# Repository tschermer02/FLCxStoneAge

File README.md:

# FLCxStoneAge Electrical Documentation

This repository contains all electrical schematics, layouts, firmware, and documentation for the StoneAge waterjet positioning system.

## Sections
- `schematics/`: Electrical schematics (PDF and source)
- `pcb/`: PCB layouts and design files
- `firmware/`: Manual and Path Following code for microcontrollers
- `components/`: Component lists and data sheets
- `installation_guides/`: Guides for assembling and wiring
- `safety_docs/`: E-Stop systems, power cutoffs, compliance notes

---

### 📥 Usage
Clone or download this repository to access the full documentation.

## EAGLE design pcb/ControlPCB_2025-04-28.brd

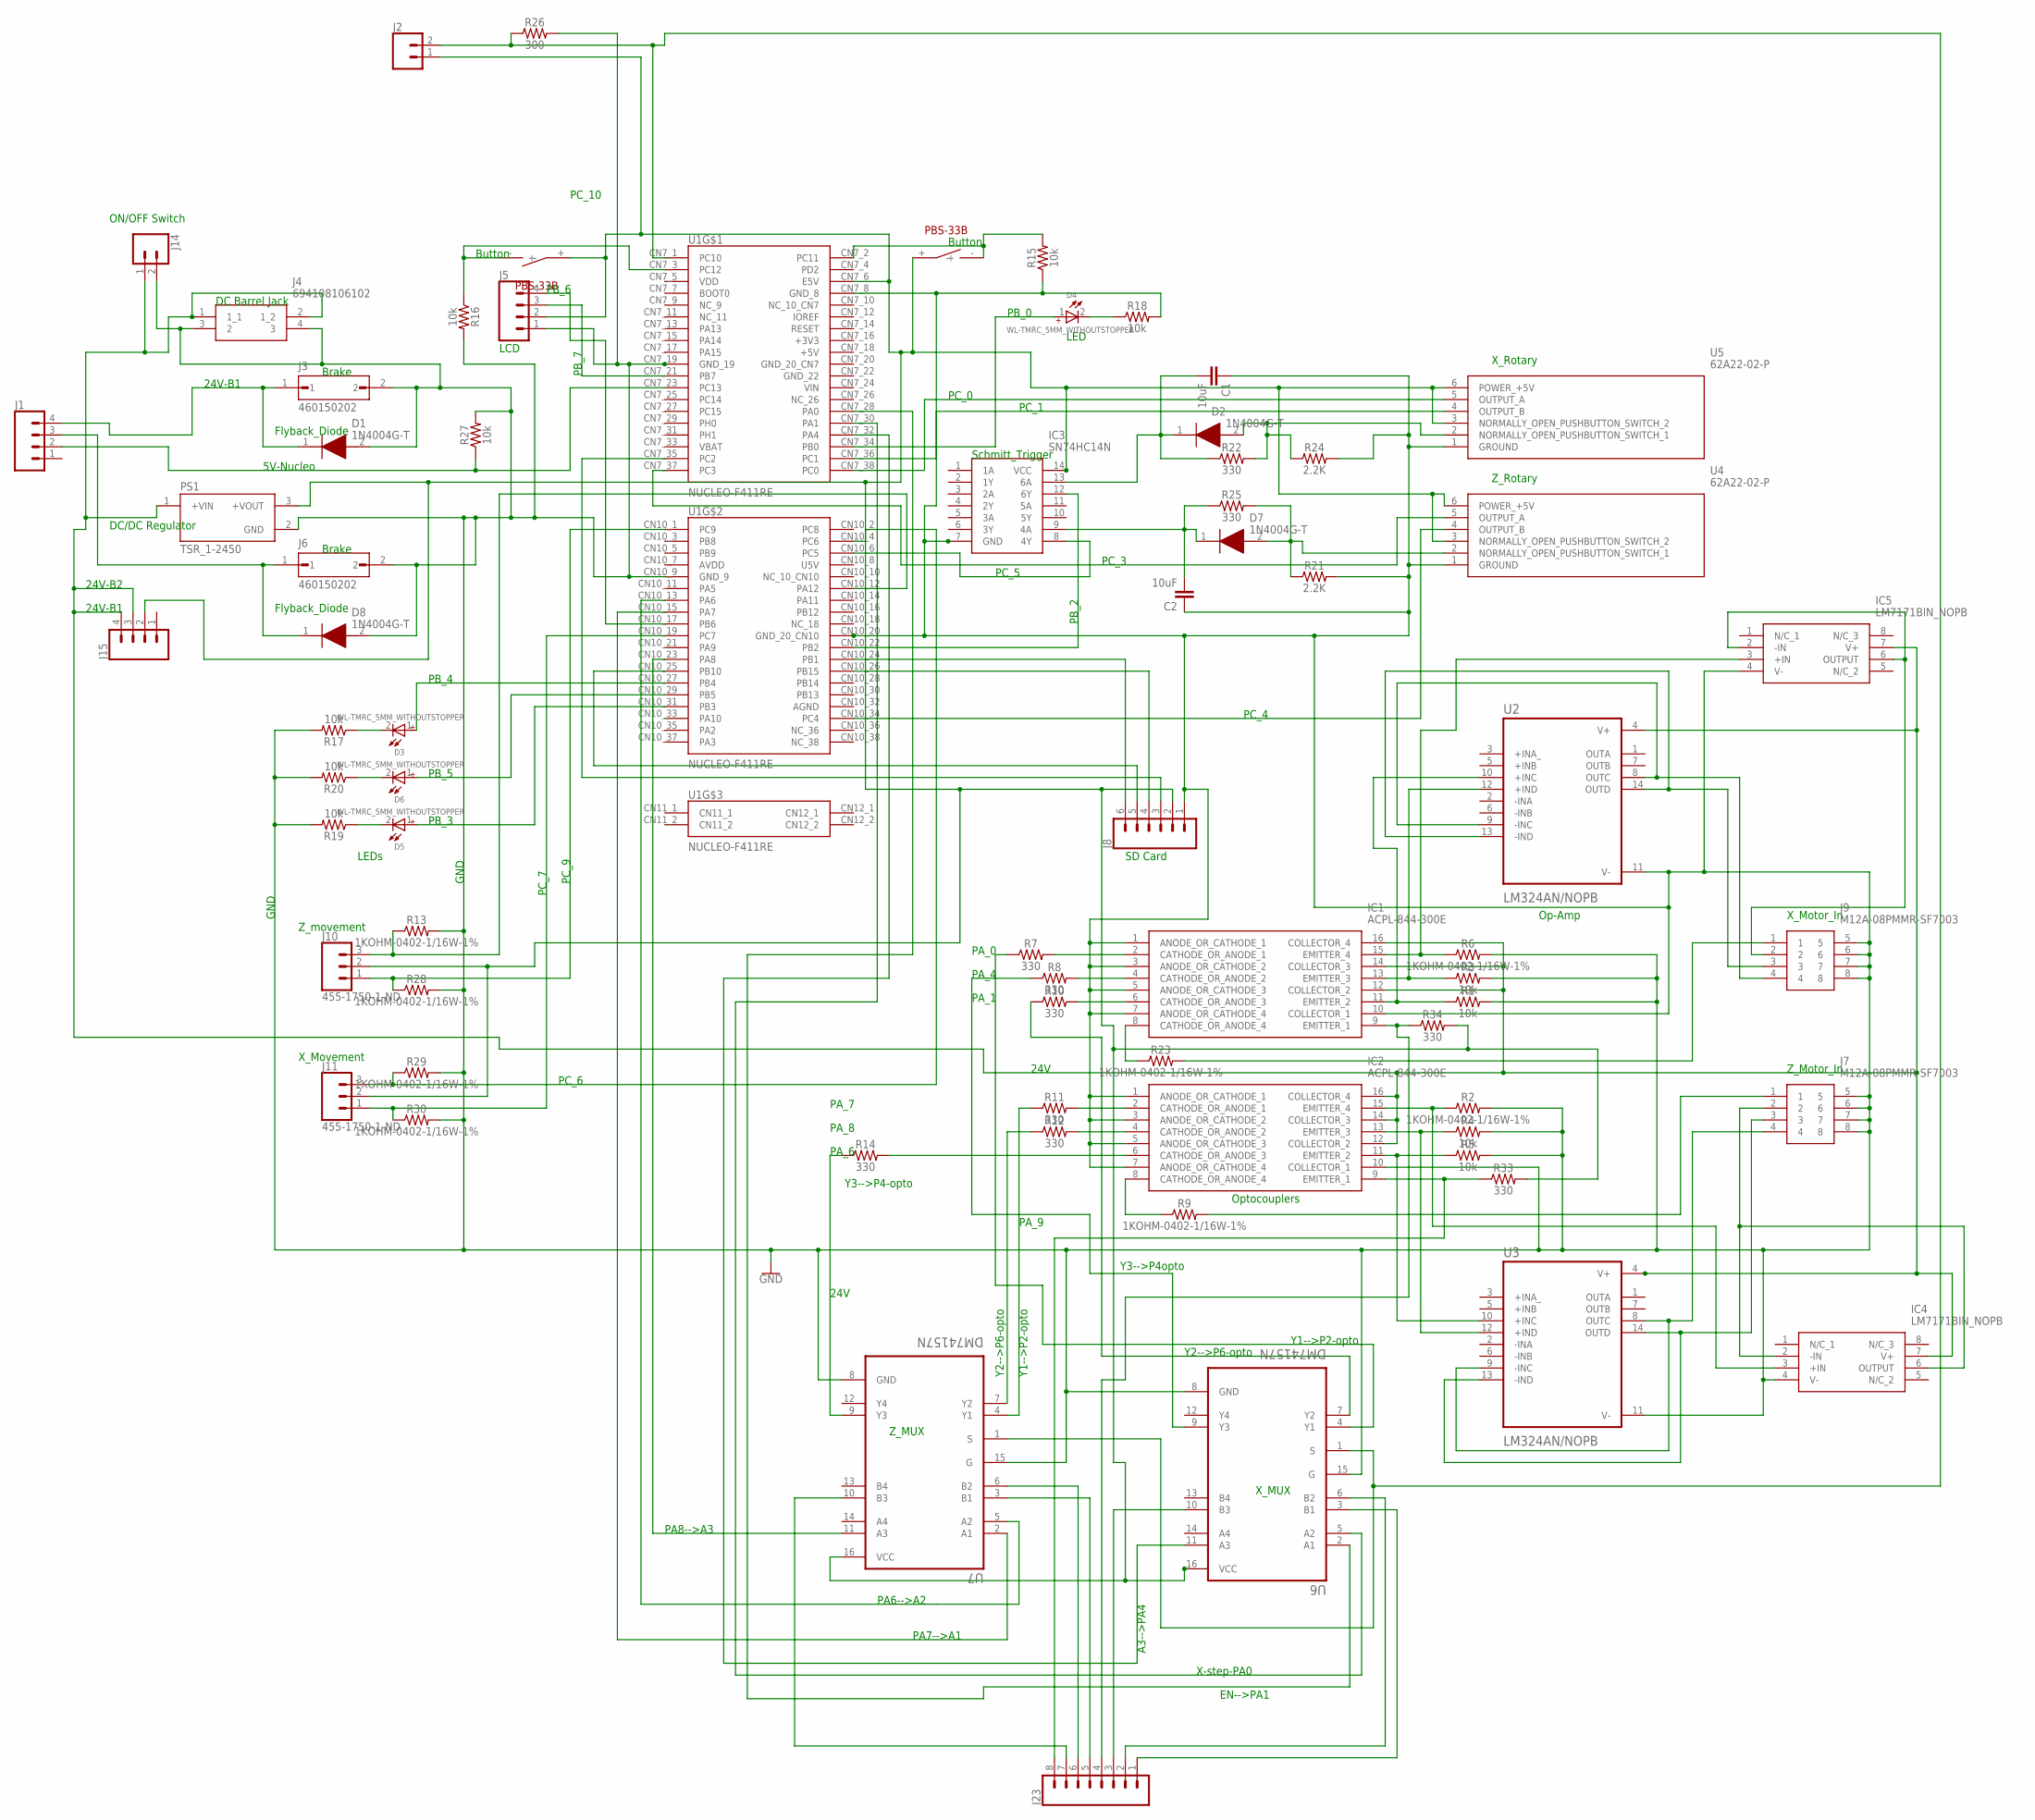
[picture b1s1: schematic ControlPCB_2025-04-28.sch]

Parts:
C1, C2: 10uF; 0603
D1, D2, D7, D8: 1N4004G-T; DIOAD1408W86L464D236
D3, D4, D5, D6: WL-TMRC_5MM_WITHOUTSTOPPER; WL-TMRC_5MM
IC1, IC2: ACPL-844-300E; DIP880W60P254L1984H450Q16N
IC3: SN74HC14N; DIP794W53P254L1930H508Q14N
IC4, IC5: LM7171BIN_NOPB; DIP794W53P254L959H508Q8N
J1, J15: CONN_04PTH; 1X04
J2, J14: CONN_02; 1X02
J3, J6: 460150202; MOLEX_460150202
J4: 694108106102
J5: CONN_04LOCK; 1X04_LOCK
J7, J9: M12A-08PMMR-SF7003; M12A08PMMRSF7003
J8: CONN_06SILK_FEMALE_PTH; 1X06
J10, J11: 455-1750-1-ND; 1X03
J23: CONN_08"; 1X08
PS1: TSR_1-2450; CONV_TSR_1-2450
R1, R3, R4, R5, R15, R16, R17, R18, R19, R20, R27: 10k; 0402
R2, R6, R9, R13, R23, R28, R29, R30: 1KOHM-0402-1/16W-1%; 0402
R7, R8, R10, R11, R12, R14, R22, R25, R33, R34: 330; 0402
R21, R24: 2.2K; 0402
R26: 300; 0603
U1: NUCLEO-F411RE; BOARD_NUCLEO-F411RE
U2, U3: LM324AN/NOPB; DIP794W45P254L1969H508Q14
U4, U5: 62A22-02-P; 62A2202P
U6, U7: DM74157N; DIP794W45P254L1918H533Q16
U$1, U$2: PBS-33B

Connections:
+3V3: U1.CN7_16 (+3V3)
+5V: U1.CN7_18 (+5V)
AGND: U1.CN10_32 (AGND)
AVDD: U1.CN10_7 (AVDD)
GND: C1.1, C2.1, D1.2 (A), D8.2 (A), IC1.1 (ANODE_OR_CATHODE_1), IC1.3 (ANODE_OR_CATHODE_2), IC1.5 (ANODE_OR_CATHODE_3), IC1.7 (ANODE_OR_CATHODE_4), IC1.10 (COLLECTOR_1), IC2.1 (ANODE_OR_CATHODE_1), IC2.3 (ANODE_OR_CATHODE_2), IC2.5 (ANODE_OR_CATHODE_3), IC2.7 (ANODE_OR_CATHODE_4), IC2.10 (COLLECTOR_1), IC3.7 (GND), IC4.4 (V-), IC5.4 (V-), J3.2, J4.3 (2), J4.4 (3), J5.1, J6.2, J7.5, J7.6, J7.7, J7.8, J8.1, J9.5, J9.6, J9.7, J9.8, J14.2, PS1.2 (GND), R1.2, R2.2, R3.2, R4.2, R5.2, R6.2, R13.2, R15.1, R16.2, R17.2, R18.2, R19.2, R20.2, R21.2, R24.2, R26.2, R27.2, R28.2, R29.2, R30.2, U1.CN7_8 (GND_8), U1.CN7_19 (GND_19), U1.CN10_9 (GND_9), U1.CN10_20 (GND_20_CN10), U2.11 (V-), U3.11 (V-), U4.1 (GROUND), U5.1 (GROUND), U6.8 (GND), U6.15 (G), U7.8 (GND), U7.15 (G)
GND_20_CN7: U1.CN7_20 (GND_20_CN7)
GND_22: U1.CN7_22 (GND_22)
unnamed: J10.1, R28.1, U1.CN10_1 (PC9)
unnamed: J9.4, U2.8 (OUTC), U2.9 (-INC)
unnamed: C2.2, D7.1 (K), IC3.9 (4A), R25.1
unnamed: IC2.9 (EMITTER_1), J23.8, R33.1
unnamed: IC2.2 (CATHODE_OR_ANODE_1), R11.2
unnamed: D8.1 (K), J1.3, J6.1
unnamed: J7.3, U3.13 (-IND), U3.14 (OUTD)
unnamed: IC2.8 (CATHODE_OR_ANODE_4), R9.1
unnamed: IC3.14 (VCC), J2.1, J5.2, J8.2, J10.2, J11.2, J15.2, PS1.3 (+VOUT), R33.2, R34.2, U1.CN7_6 (E5V), U4.3 (NORMALLY_OPEN_PUSHBUTTON_SWITCH_2), U4.6 (POWER_+5V), U5.3 (NORMALLY_OPEN_PUSHBUTTON_SWITCH_2), U5.6 (POWER_+5V), U6.16 (VCC), U7.16 (VCC), U$1.+, U$2.+
unnamed: J7.4, U3.8 (OUTC), U3.9 (-INC)
unnamed: D1.1 (K), J1.4, J3.1
unnamed: J7.1, R9.2
unnamed: IC1.4 (CATHODE_OR_ANODE_2), R8.2
unnamed: IC4.2 (-IN), IC4.6 (OUTPUT), J7.2
unnamed: R10.1, U6.7 (Y2)
unnamed: IC1.15 (EMITTER_4), IC5.3 (+IN), R6.1
unnamed: J23.7, U7.10 (B3)
unnamed: J23.6, U7.6 (B2)
unnamed: IC1.8 (CATHODE_OR_ANODE_4), R23.1
unnamed: IC5.2 (-IN), IC5.6 (OUTPUT), J9.2
unnamed: J23.5, U7.3 (B1)
unnamed: J1.2, R27.1, U1.CN7_23 (PC13)
unnamed: R16.1, U1.CN7_3 (PC12), U$2.-
unnamed: R15.2, U1.CN7_2 (PC11), U$1.-
unnamed: IC3.12 (6Y), U1.CN10_22 (PB2)
unnamed: U1.CN7_32 (PA4), U6.11 (A3)
unnamed: IC2.11 (EMITTER_2), R5.1, U3.10 (+INC)
unnamed: U1.CN7_37 (PC3), U4.5 (OUTPUT_A)
unnamed: R12.1, U7.7 (Y2)
unnamed: IC1.2 (CATHODE_OR_ANODE_1), R7.2
unnamed: IC1.12 (COLLECTOR_2), IC1.14 (COLLECTOR_3), IC1.16 (COLLECTOR_4), IC2.12 (COLLECTOR_2), IC2.14 (COLLECTOR_3), IC2.16 (COLLECTOR_4), IC4.7 (V+), IC5.7 (V+), J4.1 (1_1), J4.2 (1_2), J14.1, J15.3, J15.4, PS1.1 (+VIN), U2.4 (V+), U3.4 (V+)
unnamed: R7.1, U6.4 (Y1)
unnamed: IC1.6 (CATHODE_OR_ANODE_3), R10.2
unnamed: IC2.4 (CATHODE_OR_ANODE_2), R12.2
unnamed: U1.CN10_15 (PA7), U7.2 (A1)
unnamed: D7.2 (A), R21.1, R25.2, U4.2 (NORMALLY_OPEN_PUSHBUTTON_SWITCH_1)
unnamed: R11.1, U7.4 (Y1)
unnamed: U1.CN7_38 (PC0), U5.5 (OUTPUT_A)
unnamed: IC1.9 (EMITTER_1), J23.4, R34.1
unnamed: J9.3, U2.13 (-IND), U2.14 (OUTD)
unnamed: U1.CN10_34 (PC4), U4.4 (OUTPUT_B)
unnamed: C1.2, D2.1 (K), IC3.13 (6A), R22.1
unnamed: D4.1 (+), U1.CN7_34 (PB0)
unnamed: J5.4, U1.CN10_17 (PB6)
unnamed: D6.2 (-), R20.1
unnamed: D5.2 (-), R19.1
unnamed: D4.2 (-), R18.1
unnamed: D3.2 (-), R17.1
unnamed: J8.4, U1.CN10_26 (PB15)
unnamed: J8.5, U1.CN10_25 (PB10)
unnamed: R14.1, U7.9 (Y3)
unnamed: J9.1, R23.2
unnamed: U1.CN10_13 (PA6), U7.5 (A2)
unnamed: U1.CN7_30 (PA1), U6.5 (A2)
unnamed: U1.CN7_28 (PA0), U6.2 (A1)
unnamed: D3.1 (+), U1.CN10_27 (PB4)
unnamed: D6.1 (+), U1.CN10_29 (PB5)
unnamed: J5.3, U1.CN7_21 (PB7)
unnamed: J23.3, U6.10 (B3)
unnamed: J23.2, U6.6 (B2)
unnamed: D5.1 (+), U1.CN10_31 (PB3)
unnamed: U1.CN10_23 (PA8), U7.11 (A3)
unnamed: U1.CN7_36 (PC1), U5.4 (OUTPUT_B)
unnamed: J23.1, U6.3 (B1)
unnamed: D2.2 (A), R22.2, R24.1, U5.2 (NORMALLY_OPEN_PUSHBUTTON_SWITCH_1)
unnamed: J8.6, U1.CN10_24 (PB1)
unnamed: IC3.8 (4Y), U1.CN10_6 (PC5)
unnamed: J8.3, U1.CN7_35 (PC2)
unnamed: J2.2, R26.1, U1.CN7_1 (PC10), U6.1 (S), U7.1 (S)
unnamed: J10.3, R13.1, U1.CN10_12 (PA12)
unnamed: J11.3, R29.1, U1.CN10_4 (PC6)
unnamed: J11.1, R30.1, U1.CN10_19 (PC7)
unnamed: IC1.13 (EMITTER_3), R3.1, U2.12 (+IND)
unnamed: IC2.13 (EMITTER_3), R4.1, U3.12 (+IND)
unnamed: IC2.6 (CATHODE_OR_ANODE_3), R14.2
unnamed: R8.1, U6.9 (Y3)
unnamed: IC1.11 (EMITTER_2), R1.1, U2.10 (+INC)
unnamed: IC2.15 (EMITTER_4), IC4.3 (+IN), R2.1
U5V: U1.CN10_8 (U5V)
VBAT: U1.CN7_33 (VBAT)
VDD: U1.CN7_5 (VDD)

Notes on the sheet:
X-step-PA0
EN-->PA1
Y2-->P6-opto
A3-->PA4
Y3-->P4opto
Y1-->P2-opto
Y3-->P4-opto
ON/OFF Switch
DC Barrel Jack
Brake
Flyback_Diode
DC/DC Regulator
LEDs
X_Movement
Z_movement
SD Card
Optocouplers
Op-Amp
X_Motor_In
Z_Motor_In
Schmitt_Trigger
X_Rotary
Z_Rotary
X_MUX
Z_MUX
LED
Button
LCD
PC_9
GND
PC_6
PC_7
24V
PC_0
PC_1
PB_0
PA_0
PA_1
PA_4
PA_8

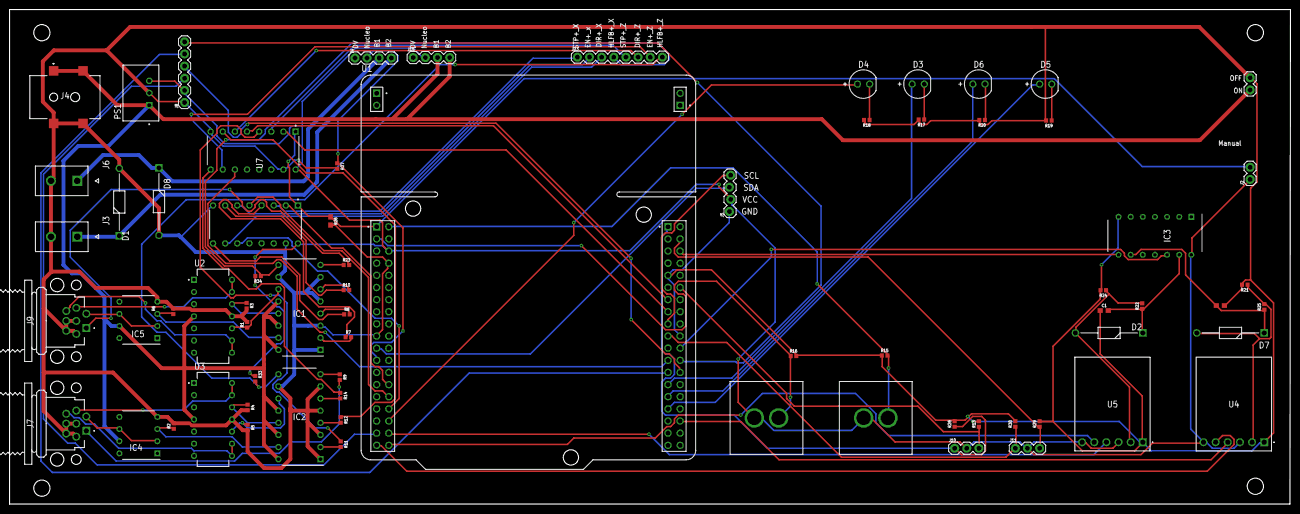
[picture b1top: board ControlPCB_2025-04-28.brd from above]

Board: 4 copper layers, 268.0 x 103.5 mm, 71 parts (0 on the bottom side), 79 nets.

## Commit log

2025-01-16 Blinking LED Test
2025-01-30 2025-01-30 UI C Code
2025-04-28 Add large file with Git LFS
2025-04-28 Add zipped UGS and STM32CubeProgrammer installers with Git LFS
2025-04-28 file upload
2025-04-28 Add zipped GSender and GRBL-Advanced software with Git LFS
2025-05-09 manual code

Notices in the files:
parts and their libraries:
SparkFun-Resistors: Licensing: Creative Commons ShareAlike 4.0 International - https://creativecommons.org/licenses/by-sa/4.0
